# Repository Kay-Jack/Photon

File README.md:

# Photon

## Description
The goal of this project was to create a simple but powerful bike LED light using my remaining 18650 batteries. This is not a weak light, it delivers strong output and can be made even more powerful by swapping two resistors (one per LED) on the current contorl ICs.

A major motivation for this project was to lower the cost of bike lights, as high-quality options are often overpriced for what they offer. I also aimed to reduce labor and assembly costs, since most units would be hand-soldered. This was done by minimizing the number of unique components on the board.

The repository includes the full schematic, PCB layout, manufacturing files, and firmware for the Photon V5 revision, currently working on V6.

## Complete
- Schematic
- Board Design 
- Testing and Validation

## WIP
- Enclosure 
- New STM32 firmware 

## Features
- **Power-Efficient Design**: Utilizes a buck converter and low-power STM32
- **Compact Size**: the board compact roughly the same size as an 18650. 
- **LED Illumination**: 3W High-brightness LEDs with current control ICs.
- **Integrated Battery Charging**: A TP4056 is used for battery charging with a bidirectional side mounted LED for indication
- **Battery Protections**: Undervoltage, overvoltage and short protection is included on the board
- **Charge Detection**: The board will automatically shut off the power to the system if it detects that the board has been plugged in for charging. 
- **Debug Header**: The board uses staggered 2.54 mm header pins that create a spring effect, allowing solderless use similar to a debug header.

## Images
### PCB Front View

### PCB Back View

### Schematic 

## Version
This is version V6 of the Photon project.

## Repository
Hosted on GitHub: [AirMatress/Photon](https://github.com/AirMatress/Photon)

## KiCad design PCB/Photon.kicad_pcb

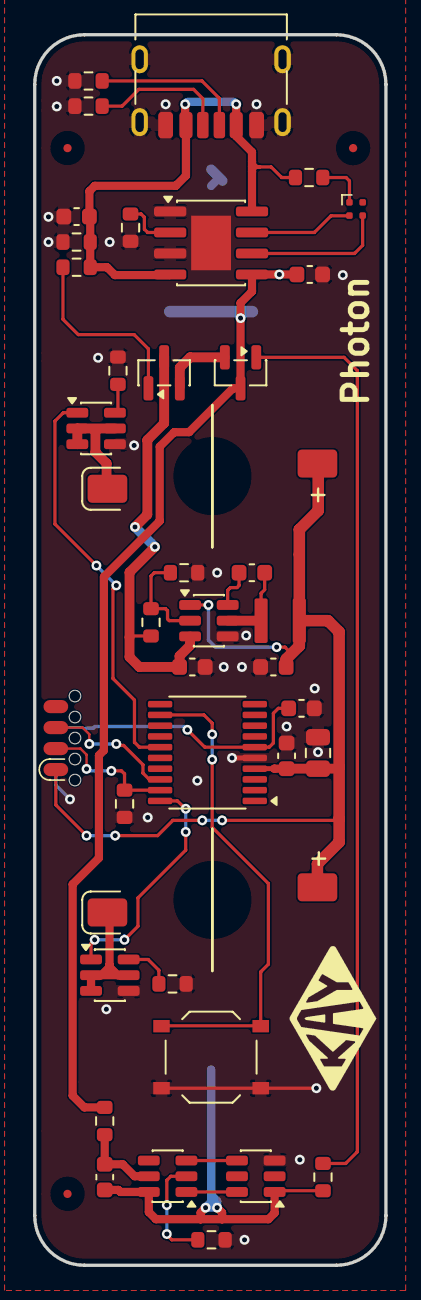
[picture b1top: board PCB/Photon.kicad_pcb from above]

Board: 2 copper layers, 21.2 x 74.4 mm, 43 parts (1 on the bottom side), 32 nets.

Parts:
BT1: Battery_Cell; 18650 Tin Strips
C1: 4.7uF; C_0805_2012Metric
C2, C6, C8, C10: 100nF; C_0603_1608Metric
C3, C4, C5: 10uF; C_0603_1608Metric
C9: 22uF; C_0603_1608Metric
D1: XL-1010RGB-YG; LED_Wurth_150044M155260
D2, D3: LED; 3W LED 9mm
FID1, FID2, FID3: Fiducial; Fiducial_0.5mm_Mask1.5mm
J1: USB_C_Receptacle_USB2.0_6P; USB_C_Receptacle_HRO_TYPE-C-31-M-17
J2: SOIC 8 Debug Clip; SOIC_clipProgSmall
L1: 4.7uH; SMD 3x3mm Power Inductor
Q1, Q2: IRLML6402; SOT-23
R1, R2: 5.1K; R_0603_1608Metric
R3, R4, R7: 2K; R_0603_1608Metric
R5: 180K; R_0603_1608Metric
R6, R8, R14: 100K; R_0603_1608Metric
R9: 10K; R_0603_1608Metric
R11: 100R; R_0603_1608Metric
R12, R15: 20R; R_0603_1608Metric
R13: 1K; R_0603_1608Metric
SW1: TS-1088-AR02016; SW_Push_1P1T_XKB_TS-1187A
U1: STM32G030F6P6TR; TSSOP-20_4.4x6.5mm_P0.65mm
U2: TP4056; SOIC-8-1EP_3.9x4.9mm_P1.27mm_EP2.41x3.3mm
U3: AP63203WU; TSOT-23-6
U4: DW01A; SOT-23-6
U5: FS8205A; SOT-23-6
U6, U7: BCR421UW6-7; SOT-23-6

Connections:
5V: C3.2, J1.A9 (VBUS), J1.B9 (VBUS), R3.1, R7.2, R8.1, U2.4 (V_{CC}), U2.8 (CE)
+3V3: C1.2, C2.1, C9.2, D2.2 (A), D3.2 (A), J2.1, L1.2, U1.4 (VDD), U3.1 (FB)
+BATT: BT1.1 (+), C5.2, Q2.3 (D), R11.1, U2.5 (BAT)
/BAT_DSBL: Q2.1 (G), R14.2
/BST: C6.2, U3.6 (BST)
/BUTN: SW1.1, U1.12 (PA5)
/Bat-: BT1.2 (-), C8.1, R14.1, U4.6 (GND), U5.1 (S1)
/CC1: J1.A5 (CC1), R1.1
/CC2: J1.B5 (CC2), R2.1
/CHRG: D1.3 (RK), U2.7 (~CHRG)
/DSBL: Q1.1 (G), R7.1
/DW01A_VCC: C8.2, R11.2, U4.5 (VCC)
/Iset: R4.1, U2.2 (PROG)
/LED_PWR: D1.1 (A), R3.2
/OC: U4.3 (OC), U5.4 (G2)
/OD: U4.1 (OD), U5.6 (G1)
/OUT_LED1: D2.1 (K), U6.2 (OUT), U6.3 (OUT), U6.5 (OUT)
/OUT_LED2: D3.1 (K), U7.2 (OUT), U7.3 (OUT), U7.5 (OUT)
/Rext1: R12.1, U6.6 (Rext)
/Rext2: R15.1, U7.6 (Rext)
/STDBY: D1.4 (GK), U2.6 (~STDBY)
/SW: C6.1, L1.1, U3.5 (SW)
/UVLO: R5.2, R6.1, U3.2 (EN)
/VBAT_SYS: C4.2, Q1.3 (D), R5.1, U3.3 (IN)
/VM: R13.2, U4.2 (VM)
GND: C1.1, C2.2, C3.1, C4.1, C5.1, C9.1, C10.1, J1.A12 (GND), J1.B12 (GND), J1.S1 (SHIELD), J2.8, R1.2, R2.2, R4.2, R6.2, R8.2, R9.2, R12.2, R13.1, R15.2, SW1.2, U1.5 (VSS), U2.1 (TEMP), U2.3 (GND), U2.9 (EPAD), U3.4 (GND), U5.3 (S2), U6.4 (GND), U7.4 (GND)
LED1_EN: U1.15 (PA8/PB0/PB1/PB2), U6.1 (EN)
LED2_EN: U1.20 (PB3/PB4/PB5/PB6), U7.1 (EN)
NRST: C10.2, J2.6, U1.6 (NRST)
PACK_SAFE: Q1.2 (S), Q2.2 (S)
SWCLK: J2.2, R9.1, U1.19 (PA14/PA15)
SWDIO: J2.3, U1.18 (PA13)

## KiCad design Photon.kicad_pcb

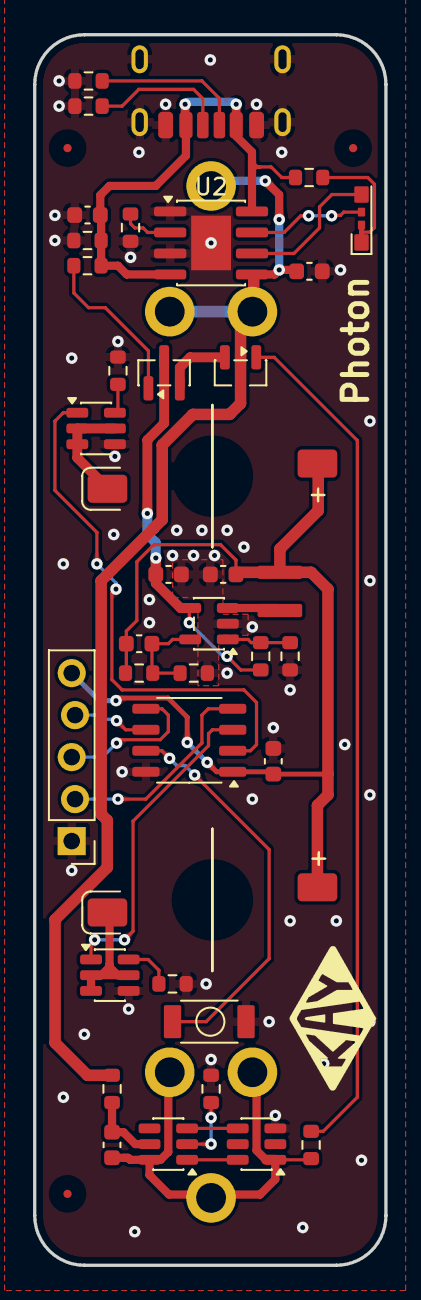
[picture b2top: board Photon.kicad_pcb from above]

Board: 2 copper layers, 21.2 x 74.4 mm, 42 parts (1 on the bottom side), 32 nets.

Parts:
BT1: Battery_Cell; Spring Battery TH
C1, C7: 100nF; C_0603_1608Metric
C2, C3, C5, C6: 10uF; C_0603_1608Metric
C4: 10pF; C_0603_1608Metric
D1: LED_Dual_AKAK; 3.9mm Bi directional side mount LED
D2, D3: LED; 3W LED 9mm
FID1, FID2, FID3: Fiducial; Fiducial_0.5mm_Mask1.5mm
J1: USB_C_Receptacle_USB2.0_14P; USB_C_Receptacle_HRO_TYPE-C-31-M-17
J2: Conn_01x05_Socket; PinHeader_1x05_P2.54mm_Vertical
L1: 2.2uH; SMD 3x3mm Power Inductor
Q1, Q2: IRLML6402; SOT-23
R1, R2: 5.1K; R_0603_1608Metric
R3: 30K; R_0603_1608Metric
R4, R7, R10: 2K; R_0603_1608Metric
R5, R6, R19: 100K; R_0603_1608Metric
R8: 280K; R_0603_1608Metric
R9: 62K; R_0603_1608Metric
R13, R16: 20R; R_0603_1608Metric
R14: 100R; R_0603_1608Metric
R17: 1K; R_0603_1608Metric
SW1: TS-1088-AR02016; 5mm Push Button
U1: PY32F002AL15S6TU; SOP-8_3.9x4.9mm_P1.27mm
U2: TP4056; SOIC-8-1EP_3.9x4.9mm_P1.27mm_EP2.41x3.3mm
U3: RT8059GJ5; SOT-23-5
U4, U7: BCR421UW6-7; SOT-23-6
U5: DW01A; SOT-23-6
U6: FS8205A; SOT-23-6

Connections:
5V: C3.2, J1.A9 (VBUS), J1.B9 (VBUS), R4.2, R5.1, R7.1, U2.4 (V_{CC}), U2.8 (CE)
+3V3: C1.2, C4.2, C5.2, D2.2 (A), D3.2 (A), J2.5, L1.2, R8.1, U1.1 (VDD)
+BATT: BT1.1 (+), C6.2, Q2.3 (D), R14.1, U2.5 (BAT)
/BAT_DSBL: Q2.1 (G), R19.2
/BTN: SW1.1, U1.7 (PA1)
/Bat-: BT1.2 (-), C7.1, R19.1, U5.6 (GND), U6.1 (S1)
/CC1: J1.A5 (CC1), R1.1
/CC2: J1.B5 (CC2), R2.1
/CHRG: D1.2 (K1), U2.7 (~CHRG)
/DSBL: Q1.1 (G), R4.1
/DW01A_VCC: C7.2, R14.2, U5.5 (VCC)
/FB: C4.1, R8.2, R9.1, U3.5 (FB)
/Iset: R10.1, U2.2 (PROG)
/LED1_EN: U1.2 (PA4/PA10), U4.1 (EN)
/LED2_EN: U1.3 (PA3), U7.1 (EN)
/LED_PWR: D1.1 (A1), D1.3 (A2), R7.2
/LX: L1.1, U3.3 (LX)
/NRST: J2.4, U1.6 (PA2/PF2/NRST)
/OC: U5.3 (OC), U6.4 (G2)
/OD: U5.1 (OD), U6.6 (G1)
/OUT_LED1: D2.1 (K), U4.2 (OUT), U4.3 (OUT), U4.5 (OUT)
/OUT_LED2: D3.1 (K), U7.2 (OUT), U7.3 (OUT), U7.5 (OUT)
/Rext1: R13.1, U4.6 (Rext)
/Rext2: R16.1, U7.6 (Rext)
/STDBY: D1.4 (K2), U2.6 (~STDBY)
/SWC: J2.2, U1.4 (PA14/PB3/SWC)
/SWD: J2.3, U1.5 (PA13/SWD)
/UVLO: R3.2, R6.1, U3.1 (EN)
/VBAT_SYS: C2.2, Q1.3 (D), R3.1, U3.4 (Vin)
/VM: R17.2, U5.2 (VM)
GND: C1.1, C2.1, C3.1, C5.1, C6.1, J1.A12 (GND), J1.B12 (GND), J1.S1 (SHIELD), J2.1, R1.2, R2.2, R5.2, R6.2, R9.2, R10.2, R13.2, R16.2, R17.1, SW1.2, U1.8 (GND), U2.1 (TEMP), U2.3 (GND), U2.9 (EPAD), U3.2 (GND), U4.4 (GND), U6.3 (S2), U7.4 (GND)
PACK_SAFE: Q1.2 (S), Q2.2 (S)

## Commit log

2025-08-03 made new pcb. and updated schematic
2025-08-08 Cleaned up schematic and PCB
2025-09-06 New Battery IC
2025-09-08 added new ic and started layout
2025-09-11 Added TP4056 back
2025-09-15 Aadjusted placement of schematic
2025-09-22 added usb detection circuit and battery protection
2025-09-25 PCB layout complete
2025-09-26 added fiducials and gerbers. - Ordered
2025-09-28 updated gerbers
2025-10-02 finished v3 of pcb
2025-10-17 v1.3
2025-11-05 Cleaned up PCB
2025-11-10 made RT805 smaller footprint, moved few parts around and center tp4056 more over battery through holes
2025-11-15 small changed and exported .step
2025-11-16 gerbers and a few components moved
2025-12-22 removing un needed parts
    - pulldowns on LEDs
    - pulldown on Buck
    - cleaned up schematic
2025-12-26 Swapped out MCU
    - not completed (WIP)
2025-12-27 Updated schem and PCB. updated footprints
2025-12-29 added stitching vias and bi direction led for charging
2025-12-31 Edged clearance resolved and programming connector modified
2025-12-31 improvements
    - added pull down to buck (previously there and was removed)
    - Simplified PCB by rotating components to reduce vias
    - updated value fields and annotated schematic
2025-12-31 small change
    Moved Q1 down .3mm
2025-12-31 added CAD files and created gerbers
2025-12-31 Gerbers updated again
2025-12-31 Added README file
2025-12-31 added .gitignore and removed backup files
2026-01-01 added UVLO for the buck
2026-01-06 updated photos and added path for step of tp4056
2026-01-06 Rotated PCB
2026-01-19 updated debug header and changed resistors for UVLO
    Applied teardrop to all vias. some were missing. Thickened trace from neg battery terminal. Updated gerbers
2026-02-16 switch to smt32 mcu and cleaned up pcb
2026-02-16 added gerbers
2026-02-16 added zip
2026-02-16 changed folder structure and added new photos
2026-02-16 Squashed commit of the following:
    commit 040f56c92c5fbfa60c6357d084ca9e817f85bd74
    Author: AirMatress <134566567+Kay-Jack@users.noreply.github.com>
    Date: Sun Feb 15 22:31:25 2026 -0500
    changed folder structure and added new photos
    commit a5de8e0470fd1fbaa1884b4c13b8efd9701bd3f9
    Author: AirMatress <134566567+Kay-Jack@users.noreply.github.com>
2026-02-16 caps too close, resolved and updated gerbers
2026-02-16 updated pcb
2026-04-08 Schematic, Board and Firmware changes
    Moved pins for LEDs onto timer channel capable pins to allow for future implementation if desired
    Added 100nF cap to NRST pin
    Changed programming footprint to use soic8 programmers found on Github
    Changed buck to diodes fixed version (AP63203WU) for fewer components
    Created Gerbers
    Updated .ioc for pinout using timer channels and naming pins to match
2026-04-08 updated silkscreen to match gerbers
2026-04-08 Pushing firmware that was previously mentioned
2026-04-08 added new inductor links
2026-04-23 Component changes for better button and LED
